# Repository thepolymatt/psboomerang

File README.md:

# PSBoomerang by polymatt

I always loved the design of the old “Boomerang” concept controller that Sony unveiled alongside the PS3 in 2005. So I built one.

You can check out the build video here: [It’s Back](https://youtu.be/1w722lkhs_E)

- Wireless over Bluetooth LE, or wired over USB-C (if you want full-fat Bluetooth, you’ll need a different microcontroller)
- Shows up as an SInput gamepad, supported by Steam and SDL3 games
- Joy-Con replacement TMR analog sticks with clickable L3/R3
- D-pad, face and center buttons using DualShock 3 replacement rubber pads on gold PCB contacts
- Built-in LiPo battery charged over USB-C; deep sleep with the Home button as soft-power switch
- Two RGB status LEDs, one of which the host can color
- Hand-solderable: no hot air or reflow needed

It won't pair with a PS3 or modern console wirelessly. The XIAO ESP32-S3 only supports Bluetooth LE, not the full-fat Bluetooth Classic the PS3 uses, plus modern consoles need authentication/negotiation.

As it stands, enjoy this one on PC, Steam, OR connected via USB on the PS3.

## What's in the repo

| Folder | Contents |
|---|---|
| `hardware/enclosure/` | Printable STLs (`stl/`) and modifiable STEPs (`step/`) |
| `hardware/pcb/controller/` | Main board KiCad project, plus gerbers, BOM, CPL and STEP in `fabrication/v0.4/` |
| `hardware/pcb/shoulder/` | Shoulder button board KiCad project, plus gerbers, BOM and CPL in `fabrication/v0.3/` |
| `hardware/pcb/lib/` | All custom and third-party symbols, footprints and 3D models the boards use |
| `firmware/PSBoomerang/` | Arduino firmware for the Seeed XIAO ESP32-S3 |
| `bom/BOM.csv` | Full parts list with part numbers and sourcing notes |
| `docs/PCB-Notes.md` | Pin map, circuit notes, assembly and soldering guide |

The KiCad projects open in KiCad 10 with no extra library setup.

You can also find the model files here: 

## Building one

1. **Order the PCBs.** Send the gerber zips from the two `fabrication/` folders to any PCB fab. Order the main board with **ENIG** finish, and two shoulder boards.
2. **Get the parts** in `bom/BOM.csv`, including a Seeed XIAO ESP32-S3 (plain, not Sense), two Joy-Con replacement sticks, DualShock 3 replacement rubber pads and a 1S LiPo with a JST-PH lead.
3. **Assemble** using `docs/PCB-Notes.md`. Check the battery connector polarity before plugging it in; it isn't standard between vendors.
4. **Print the enclosure** from `hardware/enclosure/stl/`.
5. **Flash the firmware** (below).
6. Have fun.

## Firmware setup

1. Install the [Arduino IDE](https://www.arduino.cc/en/software) and the **esp32** board package by Espressif (Boards Manager).
2. Install these libraries:
   - [ESP32-BLE-Gamepad](https://github.com/lemmingDev/ESP32-BLE-Gamepad) by lemmingDev, a version with SInput support (install from GitHub if the Library Manager version doesn't include `BleSInput.h`)
   - NimBLE-Arduino
   - Adafruit NeoPixel
3. Open `firmware/PSBoomerang/PSBoomerang.ino`, select the **XIAO_ESP32S3** board and set:

   | Tools setting | Value |
   |---|---|
   | USB CDC On Boot | Enabled |
   | USB Mode | USB-OTG (TinyUSB) |
   | Upload Mode | USB-OTG CDC (TinyUSB) |

4. Upload. If no port shows up, hold the XIAO's BOOT button while plugging it in.

Options such as stick orientation and face-button order are at the top of `Config.h`.

## Using it

| Action | How |
|---|---|
| Wake | Hold Home for 1 s |
| Sleep | Hold Home for 3 s. It also sleeps after 10 minutes without input on battery. |
| Pair | The status LED breathes blue while it's waiting. Pair with **PSBoomerang** in your Bluetooth settings. |
| Wired | Plug USB-C into a computer. USB takes over from Bluetooth while connected. |
| Calibrate sticks | Hold Select + L3 + R3 for 3 s, then release. Keep hands off while the LED blinks white. When it turns magenta, circle both sticks to their limits, then press Start. Green means saved, red means try again. |

Calibrate the sticks once after the first flash - if needed.

**Status LED:** green, amber or red shows the battery level (above 50%, above 20%, 20% and below). It breathes while charging. Blinking red means the button expander isn't responding.

## License

The PSBoomerang was designed by me, polymatt, and Copyright (c) 2026 Unscripted Engineering, LLC.

The hardware is licensed under CERN-OHL-S-2.0 and the firmware under GPL-3.0-or-later. You're free to build, modify and sell it, as long as anything you share stays under the same license. See [LICENSE.md](LICENSE.md).

PSBoomerang is an independent project and isn't affiliated with or endorsed by Sony Interactive Entertainment. PlayStation and DualShock are trademarks of Sony Interactive Entertainment.

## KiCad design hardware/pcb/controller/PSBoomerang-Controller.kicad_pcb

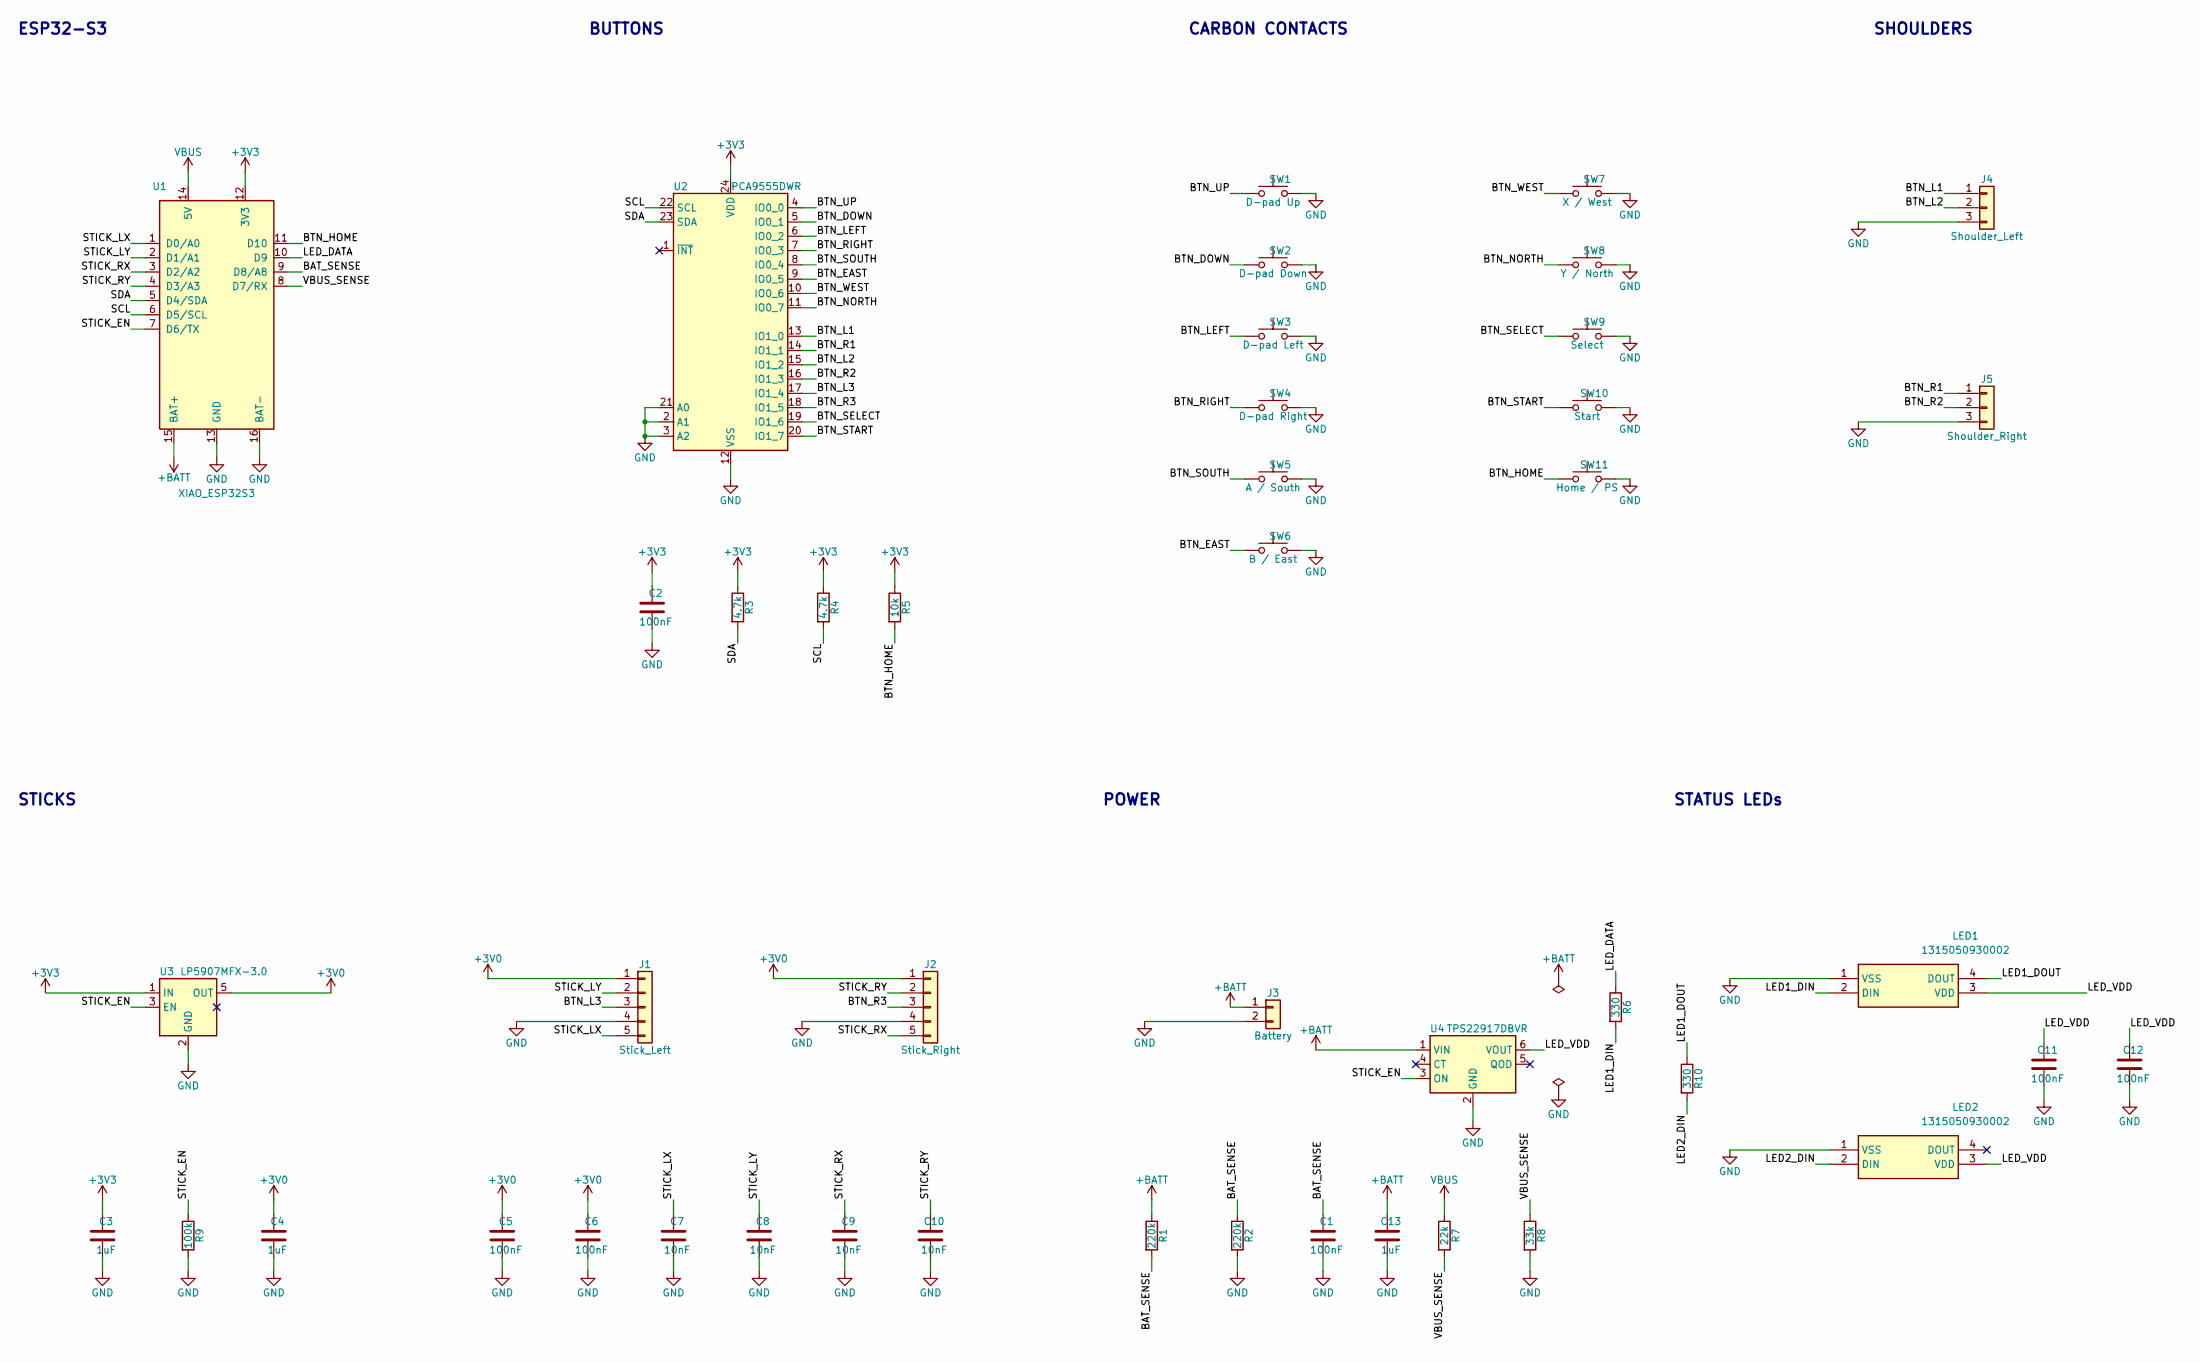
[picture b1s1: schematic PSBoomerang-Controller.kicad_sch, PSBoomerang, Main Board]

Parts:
C1, C2, C5, C6, C11, C12: 100nF; C_0805_2012Metric_Pad1.18x1.45mm_HandSolder; MPN CC0805KRX7R9BB104
C3, C4, C13: 1uF; C_0805_2012Metric_Pad1.18x1.45mm_HandSolder; MPN 08055C105KAT2A
C7, C8, C9, C10: 10nF; C_0805_2012Metric_Pad1.18x1.45mm_HandSolder; MPN CL21B103KBANNNC
J1: Stick_Left; 5051100592; MPN 5051100592
J2: Stick_Right; 5051100592; MPN 5051100592
J3: Battery; JST_PH_B2B-PH-SM4-TB_1x02-1MP_P2.00mm_Vertical; MPN B2B-PH-SM4-TB(LF)(SN)
J4: Shoulder_Left; JST_PH_S3B-PH-SM4-TB_1x03-1MP_P2.00mm_Horizontal; MPN S3B-PH-SM4-TB(LF)(SN)
J5: Shoulder_Right; JST_PH_S3B-PH-SM4-TB_1x03-1MP_P2.00mm_Horizontal; MPN S3B-PH-SM4-TB(LF)(SN)
LED1, LED2: 1315050930002; LED_1315050930002_HandSolder
R1, R2: 220k; R_0805_2012Metric_Pad1.20x1.40mm_HandSolder; MPN RC0805FR-07220KL
R3, R4: 4.7k; R_0805_2012Metric_Pad1.20x1.40mm_HandSolder; MPN RC0805FR-074K7L
R5: 10k; R_0805_2012Metric_Pad1.20x1.40mm_HandSolder; MPN RC0805FR-0710KL
R6, R10: 330; R_0805_2012Metric_Pad1.20x1.40mm_HandSolder; MPN RC0805FR-07330RL
R7: 22k; R_0805_2012Metric_Pad1.20x1.40mm_HandSolder; MPN RC0805FR-0722KL
R8: 33k; R_0805_2012Metric_Pad1.20x1.40mm_HandSolder; MPN RC0805FR-0733KL
R9: 100k; R_0805_2012Metric_Pad1.20x1.40mm_HandSolder; MPN RC0805FR-07100KL
SW1: D-pad Up; CarbonPad_DPad
SW2: D-pad Down; CarbonPad_DPad
SW3: D-pad Left; CarbonPad_DPad
SW4: D-pad Right; CarbonPad_DPad
SW5: A / South; CarbonPad_Face
SW6: B / East; CarbonPad_Face
SW7: X / West; CarbonPad_Face
SW8: Y / North; CarbonPad_Face
SW9: Select; CarbonPad_2Pill
SW10: Start; CarbonPad_2Pill
SW11: Home / PS; CarbonPad_3Pill
U1: XIAO_ESP32S3; XIAO_ESP32S3_Carrier; MPN 113991114
U2: PCA9555DWR; SOIC-24W_7.5x15.4mm_P1.27mm; MPN PCA9555DWR
U3: LP5907MFX-3.0; SOT-23-5_HandSoldering; MPN LP5907MFX-3.0/NOPB
U4: TPS22917DBVR; SOT-23-6_Handsoldering; MPN TPS22917DBVR

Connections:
+3V0: C4.1, C5.1, C6.1, J1.1, J2.1, U3.5 (OUT)
+3V3: C2.1, C3.1, R3.1, R4.1, R5.1, U1.12 (3V3), U2.24 (VDD), U3.1 (IN)
+BATT: C13.1, J3.1, R1.1, U1.15 (BAT+), U4.1 (VIN)
/BAT_SENSE: C1.1, R1.2, R2.1, U1.9 (D8/A8)
/BTN_DOWN: SW2.1, U2.5 (IO0_1)
/BTN_EAST: SW6.1, U2.9 (IO0_5)
/BTN_HOME: R5.2, SW11.1, U1.11 (D10)
/BTN_L1: J4.1, U2.13 (IO1_0)
/BTN_L2: J4.2, U2.15 (IO1_2)
/BTN_L3: J1.3, U2.17 (IO1_4)
/BTN_LEFT: SW3.1, U2.6 (IO0_2)
/BTN_NORTH: SW8.1, U2.11 (IO0_7)
/BTN_R1: J5.1, U2.14 (IO1_1)
/BTN_R2: J5.2, U2.16 (IO1_3)
/BTN_R3: J2.3, U2.18 (IO1_5)
/BTN_RIGHT: SW4.1, U2.7 (IO0_3)
/BTN_SELECT: SW9.1, U2.19 (IO1_6)
/BTN_SOUTH: SW5.1, U2.8 (IO0_4)
/BTN_START: SW10.1, U2.20 (IO1_7)
/BTN_UP: SW1.1, U2.4 (IO0_0)
/BTN_WEST: SW7.1, U2.10 (IO0_6)
/LED1_DIN: LED1.2 (DIN), R6.2
/LED1_DOUT: LED1.4 (DOUT), R10.1
/LED2_DIN: LED2.2 (DIN), R10.2
/LED_DATA: R6.1, U1.10 (D9)
/LED_VDD: C11.1, C12.1, LED1.3 (VDD), LED2.3 (VDD), U4.6 (VOUT)
/SCL: R4.2, U1.6 (D5/SCL), U2.22 (SCL)
/SDA: R3.2, U1.5 (D4/SDA), U2.23 (SDA)
/STICK_EN: R9.1, U1.7 (D6/TX), U3.3 (EN), U4.3 (ON)
/STICK_LX: C7.1, J1.5, U1.1 (D0/A0)
/STICK_LY: C8.1, J1.2, U1.2 (D1/A1)
/STICK_RX: C9.1, J2.5, U1.3 (D2/A2)
/STICK_RY: C10.1, J2.2, U1.4 (D3/A3)
/VBUS_SENSE: R7.2, R8.1, U1.8 (D7/RX)
GND: C1.2, C2.2, C3.2, C4.2, C5.2, C6.2, C7.2, C8.2, C9.2, C10.2, C11.2, C12.2, C13.2, J1.4, J2.4, J3.2, J4.3, J5.3, LED1.1 (VSS), LED2.1 (VSS), R2.2, R8.2, R9.2, SW1.2, SW2.2, SW3.2, SW4.2, SW5.2, SW6.2, SW7.2, SW8.2, SW9.2, SW10.2, SW11.2, U1.13 (GND), U1.16 (BAT-), U2.2 (A1), U2.3 (A2), U2.12 (VSS), U2.21 (A0), U3.2 (GND), U4.2 (GND)
VBUS: R7.1, U1.14 (5V)

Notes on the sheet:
STATUS LEDs
ESP32-S3
STICKS
POWER
CARBON CONTACTS
SHOULDERS
BUTTONS

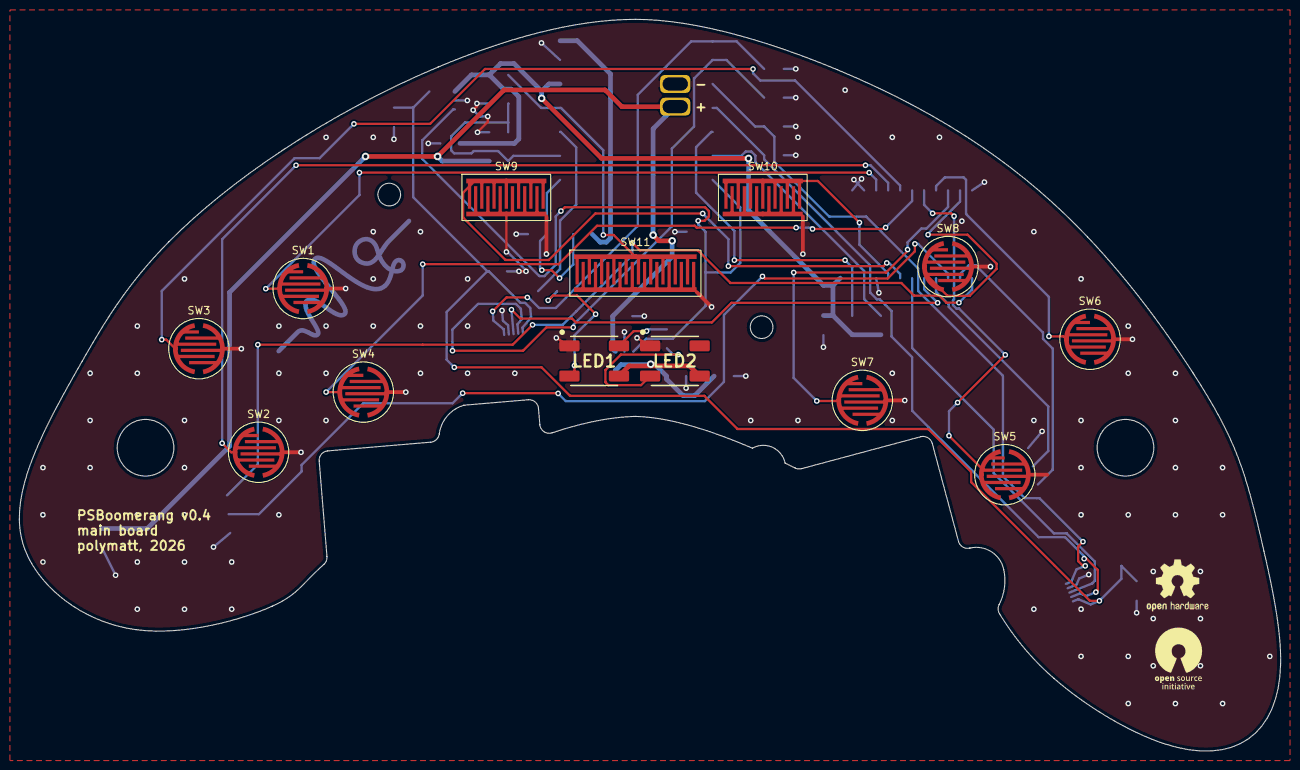
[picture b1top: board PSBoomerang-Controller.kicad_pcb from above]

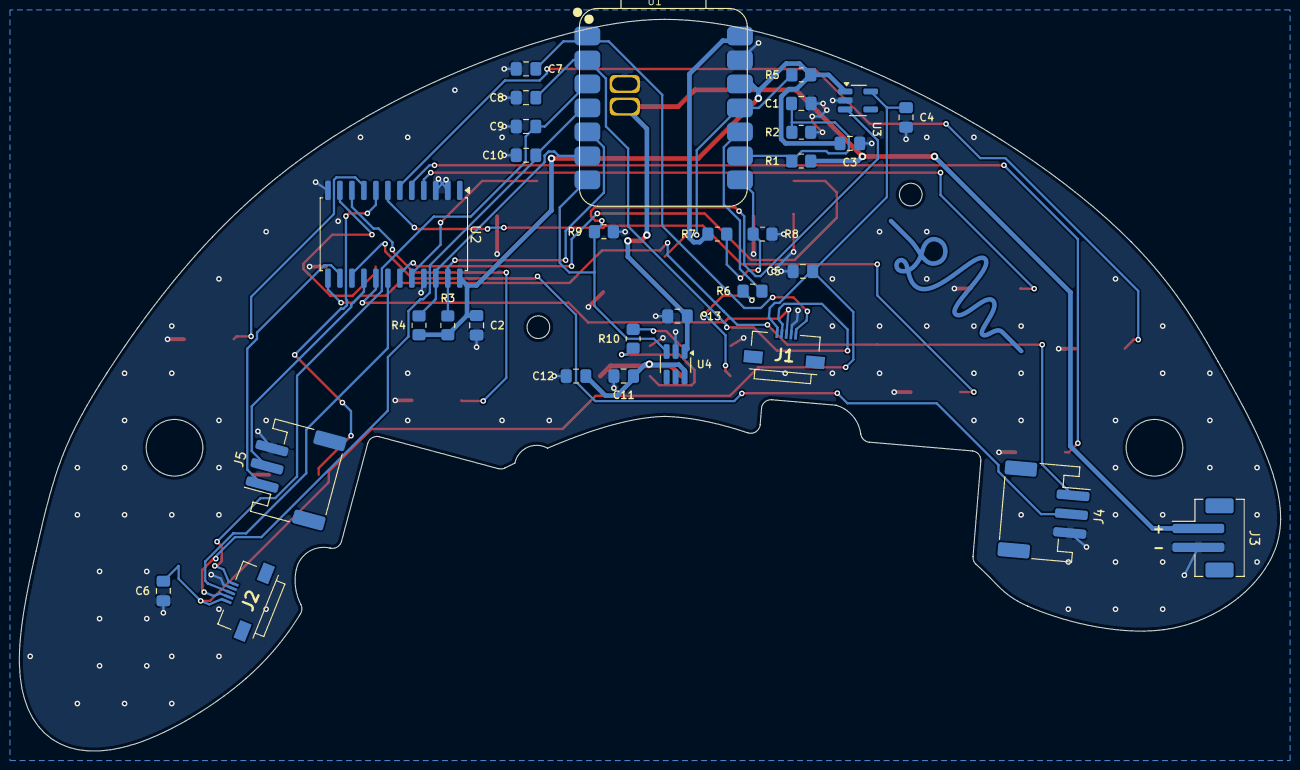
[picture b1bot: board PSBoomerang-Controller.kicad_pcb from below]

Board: 2 copper layers, 133.7 x 77.5 mm, 45 parts (32 on the bottom side), 36 nets.

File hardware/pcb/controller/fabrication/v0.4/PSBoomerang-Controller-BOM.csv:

Item,Designator,Qty,Manufacturer,Mfg Part #,Description,Package,Type,Side,Notes
1,U1,1,Seeed Studio,113991114,"XIAO ESP32S3 module (plain, not Sense)",Castellated module 21 x 17.8 mm,SMD,Bottom,"Bottom side; USB-C overhangs the board edge by design. Reflow pads 1-14. After reflow, hand-solder the module's BAT+/BAT- underside pads from the TOP side through the two plated slots (no paste in the slots; do not bridge them: battery short)"
2,U2,1,Texas Instruments,PCA9555DWR,16-bit I2C I/O expander,SOIC-24 wide (7.5 mm),SMD,Bottom,"Do not substitute: footprint is SOIC-24 (TCA9555 is TSSOP only)"
3,U3,1,Texas Instruments,LP5907MFX-3.0/NOPB,"LDO 3.0 V 250 mA, with enable",SOT-23-5,SMD,Bottom,
4,U4,1,Texas Instruments,TPS22917DBVR,"Load switch 5.5 V 2 A, active-high ON",SOT-23-6,SMD,Bottom,Do not substitute
5,"J1, J2",2,Molex,5051100592,"FFC/FPC connector 5-pos 0.5 mm pitch, bottom contact, right angle",SMD,SMD,Bottom,Do not substitute (must be bottom contact)
6,J3,1,JST,B2B-PH-SM4-TB(LF)(SN),"PH 2-pin header, vertical (top entry)",SMD,SMD,Bottom,
7,"J4, J5",2,JST,S3B-PH-SM4-TB(LF)(SN),"PH 3-pin header, side entry",SMD,SMD,Bottom,
8,"LED1, LED2",2,Wurth Elektronik,1315050930002,WL-ICLED addressable RGB LED (WS2812 protocol),PLCC4 5.0 x 5.4 mm,SMD,Top,"Top side. MSL 3. Pin 1 = chamfered-corner orientation mark, at the silkscreen dot"
9,"C1, C2, C5, C6, C11, C12",6,Yageo,CC0805KRX7R9BB104,Capacitor 100 nF 50 V X7R 10%,0805,SMD,Bottom,Equivalent 0805 X7R >=25 V OK
10,"C3, C4, C13",3,KYOCERA AVX,08055C105KAT2A,Capacitor 1 uF 50 V X7R 10%,0805,SMD,Bottom,Equivalent 0805 X7R >=25 V OK
11,"C7, C8, C9, C10",4,Samsung Electro-Mechanics,CL21B103KBANNNC,Capacitor 10 nF 50 V X7R 10%,0805,SMD,Bottom,Equivalent 0805 X7R >=25 V OK
12,"R1, R2",2,Yageo,RC0805FR-07220KL,Resistor 220 kohm 1%,0805,SMD,Bottom,Equivalent 0805 1% thick film OK
13,"R3, R4",2,Yageo,RC0805FR-074K7L,Resistor 4.7 kohm 1%,0805,SMD,Bottom,Equivalent 0805 1% thick film OK
14,R5,1,Yageo,RC0805FR-0710KL,Resistor 10 kohm 1%,0805,SMD,Bottom,Equivalent 0805 1% thick film OK
15,"R6, R10",2,Yageo,RC0805FR-07330RL,Resistor 330 ohm 1%,0805,SMD,Bottom,Equivalent 0805 1% thick film OK
16,R7,1,Yageo,RC0805FR-0722KL,Resistor 22 kohm 1%,0805,SMD,Bottom,Equivalent 0805 1% thick film OK
17,R8,1,Yageo,RC0805FR-0733KL,Resistor 33 kohm 1%,0805,SMD,Bottom,Equivalent 0805 1% thick film OK
18,R9,1,Yageo,RC0805FR-07100KL,Resistor 100 kohm 1%,0805,SMD,Bottom,Equivalent 0805 1% thick film OK

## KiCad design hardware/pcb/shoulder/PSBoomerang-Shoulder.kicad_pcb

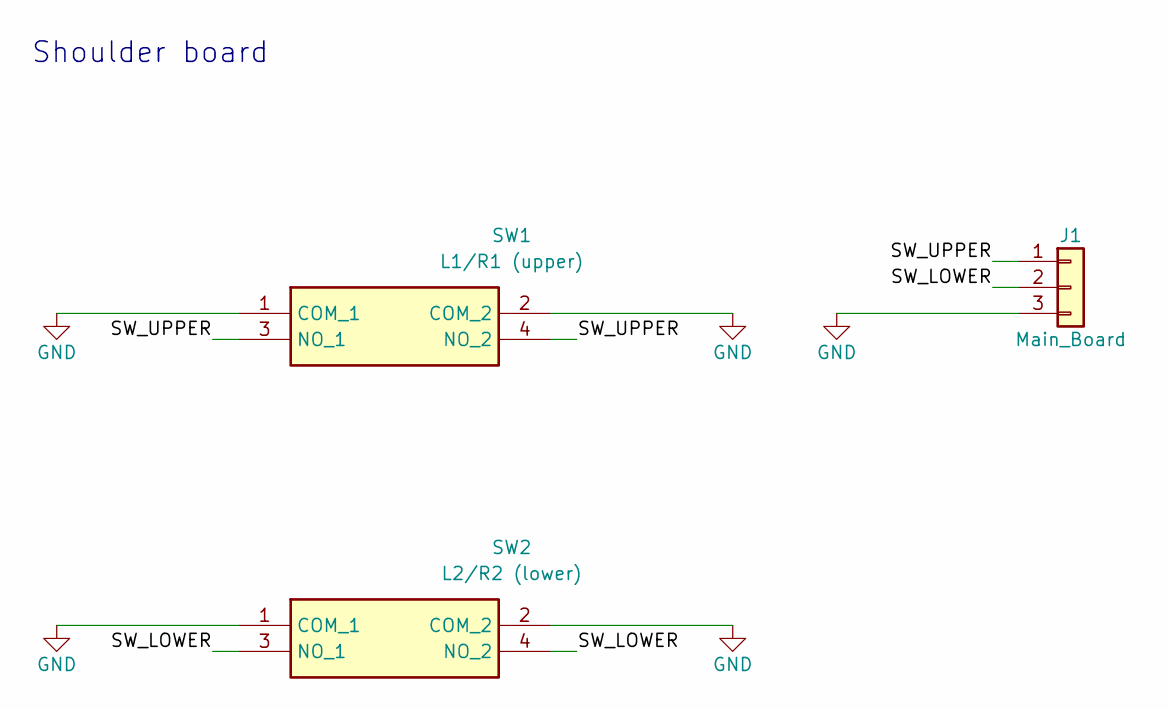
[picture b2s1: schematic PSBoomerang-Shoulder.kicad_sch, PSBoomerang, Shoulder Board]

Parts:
J1: Main_Board; JST_PH_S3B-PH-SM4-TB_1x03-1MP_P2.00mm_Horizontal; MPN S3B-PH-SM4-TB(LF)(SN)
SW1: L1/R1 (upper); PTS526SM15SMTR2LFS; MPN PTS526 SM15 SMTR2 LFS
SW2: L2/R2 (lower); PTS526SM15SMTR2LFS; MPN PTS526 SM15 SMTR2 LFS

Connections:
/SW_LOWER: J1.2, SW2.3 (NO_1), SW2.4 (NO_2)
/SW_UPPER: J1.1, SW1.3 (NO_1), SW1.4 (NO_2)
GND: J1.3, SW1.1 (COM_1), SW1.2 (COM_2), SW2.1 (COM_1), SW2.2 (COM_2)

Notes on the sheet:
Shoulder board

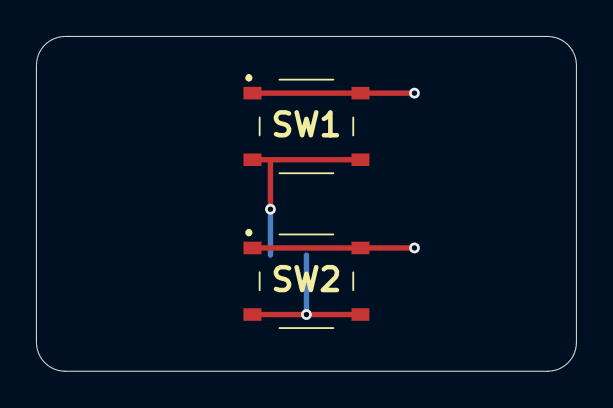
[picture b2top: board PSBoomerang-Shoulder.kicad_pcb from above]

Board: 2 copper layers, 30.0 x 18.6 mm, 3 parts (1 on the bottom side), 3 nets.

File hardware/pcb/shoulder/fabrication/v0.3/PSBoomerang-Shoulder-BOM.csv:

Item,Designator,Qty,Manufacturer,Mfg Part #,Description,Package,Type,Side,Notes
1,J1,1,JST,S3B-PH-SM4-TB(LF)(SN),"PH 3-pin header, side entry",SMD,SMD,Bottom,
2,"SW1, SW2",2,C&K,PTS526 SM15 SMTR2 LFS,"Tactile switch 5.2 x 5.2 x 1.5 mm, top actuated",SMD,SMD,Top,Top side

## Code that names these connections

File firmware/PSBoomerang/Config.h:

// PSBoomerang by polymatt. Copyright (c) 2026 Unscripted Engineering, LLC.
// https://github.com/thepolymatt/psboomerang
// Licensed under the GNU GPL v3.0 or later. See LICENSE.md in the repository root.
// SPDX-License-Identifier: GPL-3.0-or-later

// Board configuration: pins, button map, tuning. Pins match the main board (see the pin map in docs/PCB-Notes.md).
#pragma once
#include <Arduino.h>

// With USB CDC On Boot disabled, Serial is UART0 on GPIO43/44, which are STICK_EN and VBUS_SENSE here.
#if !ARDUINO_USB_CDC_ON_BOOT
#error "Set Tools > USB CDC On Boot > Enabled (Serial must not use GPIO43/44)"
#endif
// Wired mode adds a USB gamepad next to the serial port, which needs the TinyUSB stack.
#if ARDUINO_USB_MODE
#error "Set Tools > USB Mode > USB-OTG (TinyUSB), and Tools > Upload Mode > USB-OTG CDC (TinyUSB)"
#endif

#define DEVICE_NAME         "PSBoomerang"
#define DEVICE_MANUFACTURER "polymatt"

// ---- XIAO ESP32-S3 pin plan ----
constexpr uint8_t PIN_STICK_LX   = A0;  // D0 / GPIO1
constexpr uint8_t PIN_STICK_LY   = A1;  // D1 / GPIO2
constexpr uint8_t PIN_STICK_RX   = A2;  // D2 / GPIO3
constexpr uint8_t PIN_STICK_RY   = A3;  // D3 / GPIO4
constexpr uint8_t PIN_I2C_SDA    = D4;  // GPIO5
constexpr uint8_t PIN_I2C_SCL    = D5;  // GPIO6
constexpr uint8_t PIN_STICK_EN   = D6;  // GPIO43 (UART TX, toggles during boot log; harmless here), stick LDO (U3) + LED load switch (U4) enable
constexpr uint8_t PIN_VBUS_SENSE = D7;  // GPIO44 (UART RX, input at boot), USB 5V through a 22k/33k divider
constexpr uint8_t PIN_BATTERY    = A8;  // D8 / GPIO7, battery through a 220k/220k divider
constexpr uint8_t PIN_LED        = D9;  // GPIO8, WS2812 data in
constexpr uint8_t PIN_HOME       = D10; // GPIO9, Home/PS button to GND, 10k pull-up (RTC-capable: the wake-from-sleep button)

// ---- PCA9555 button expander (TCA9555 is register- and pin-compatible) ----
constexpr uint8_t EXPANDER_I2C_ADDR = 0x20; // A0-A2 tied to GND
constexpr uint32_t I2C_CLOCK_HZ     = 400000;

// Bits 0-15 are the expander pins (P00-P07 = bits 0-7, P10-P17 = bits 8-15); reorder
// freely to suit the PCB routing. BTN_HOME is wired straight to the XIAO (PIN_HOME).
enum ButtonBit : uint8_t
{
  BTN_DPAD_UP = 0,  // P00
  BTN_DPAD_DOWN,    // P01
  BTN_DPAD_LEFT,    // P02
  BTN_DPAD_RIGHT,   // P03
  BTN_SOUTH,        // P04  A / Cross
  BTN_EAST,         // P05  B / Circle
  BTN_WEST,         // P06  X / Square
  BTN_NORTH,        // P07  Y / Triangle
  BTN_L1,           // P10
  BTN_R1,           // P11
  BTN_L2,           // P12
  BTN_R2,           // P13
  BTN_L3,           // P14  left stick click
  BTN_R3,           // P15  right stick click
  BTN_SELECT,       // P16
  BTN_START,        // P17
  BTN_HOME,         // PIN_HOME (PS / Guide)
  BUTTON_BIT_COUNT
};

constexpr uint8_t BUTTON_DEBOUNCE_MS = 5; // lockout after an edge; the first edge is reported immediately

// ---- Sticks ----
constexpr uint8_t STICK_OVERSAMPLE = 4;      // ADC reads averaged per axis per scan
constexpr float   STICK_DEADZONE_INNER = 0.06f; // radial, fraction of full deflection
constexpr float   STICK_DEADZONE_OUTER = 0.95f; // deflection at or beyond this reports 100%
constexpr int     STICK_DEFAULT_HALF_RANGE_MV = 1100; // used until the first calibration is saved

// Flip these so that, relative to the stick's own body, right = +X and down = +Y (SDL convention),
// i.e. what you'd want if the stick were mounted upright.
constexpr bool INVERT_LX = false;
constexpr bool INVERT_LY = false;
constexpr bool INVERT_RX = false;
constexpr bool INVERT_RY = false;

// Angle each stick is mounted at, in degrees clockwise as seen from the front of the controller.
// Any angle works (90, -90, 30...). Calibration is unaffected: it runs in the stick's own axes.
// To check: with DEBUG_INPUT on, push straight up and confirm the output is (0, -32767).
constexpr float STICK_L_MOUNT_DEG = 180.0f;
constexpr float STICK_R_MOUNT_DEG = -100.0f;

// ---- Face buttons ----
// SInput hosts (Steam, SDL3 games) place the face buttons by position: false is correct there.
// Hosts that see a generic gamepad (Safari, and so joypad.ai on a Mac) read them in Nintendo order,
// which swaps top with left and bottom with right. true pre-swaps them for those hosts, and then
// they read swapped in Steam instead.
constexpr bool SWAP_FACE_BUTTONS = true;

// ---- Chords ----
// Holding Select + L3 + R3 for this long enters stick calibration.
constexpr uint32_t CALIBRATION_HOLD_MS = 3000;

// ---- Battery ----
constexpr float    BATTERY_DIVIDER_RATIO = 2.0f; // 220k / 220k
constexpr uint32_t BATTERY_SAMPLE_MS = 1000;

// ---- Power ----
// The controller deep-sleeps (~25 uA) and a long press of Home wakes it.
constexpr uint32_t SLEEP_HOLD_MS = 3000;           // hold Home this long to sleep
constexpr uint32_t WAKE_HOLD_MS  = 1000;           // and this long to wake; shorter presses go back to sleep
constexpr uint32_t IDLE_SLEEP_MS = 10 * 60 * 1000; // sleep after this long without input, on battery only

// ---- Status LED ----
constexpr uint8_t LED_COUNT = 2;
constexpr uint8_t LED_BRIGHTNESS = 40; // 0-255; these sit close to the player's eyes
constexpr float   LED_MIN_VBAT = 3.5f; // Würth WL-ICLED minimum VDD; LEDs run from the battery

// ---- Reporting ----
constexpr uint32_t REPORT_MIN_INTERVAL_US = 5000; // cap BLE reports at 200 Hz
constexpr bool DEBUG_INPUT = true; // print raw stick mV and button bits to Serial at 10 Hz
